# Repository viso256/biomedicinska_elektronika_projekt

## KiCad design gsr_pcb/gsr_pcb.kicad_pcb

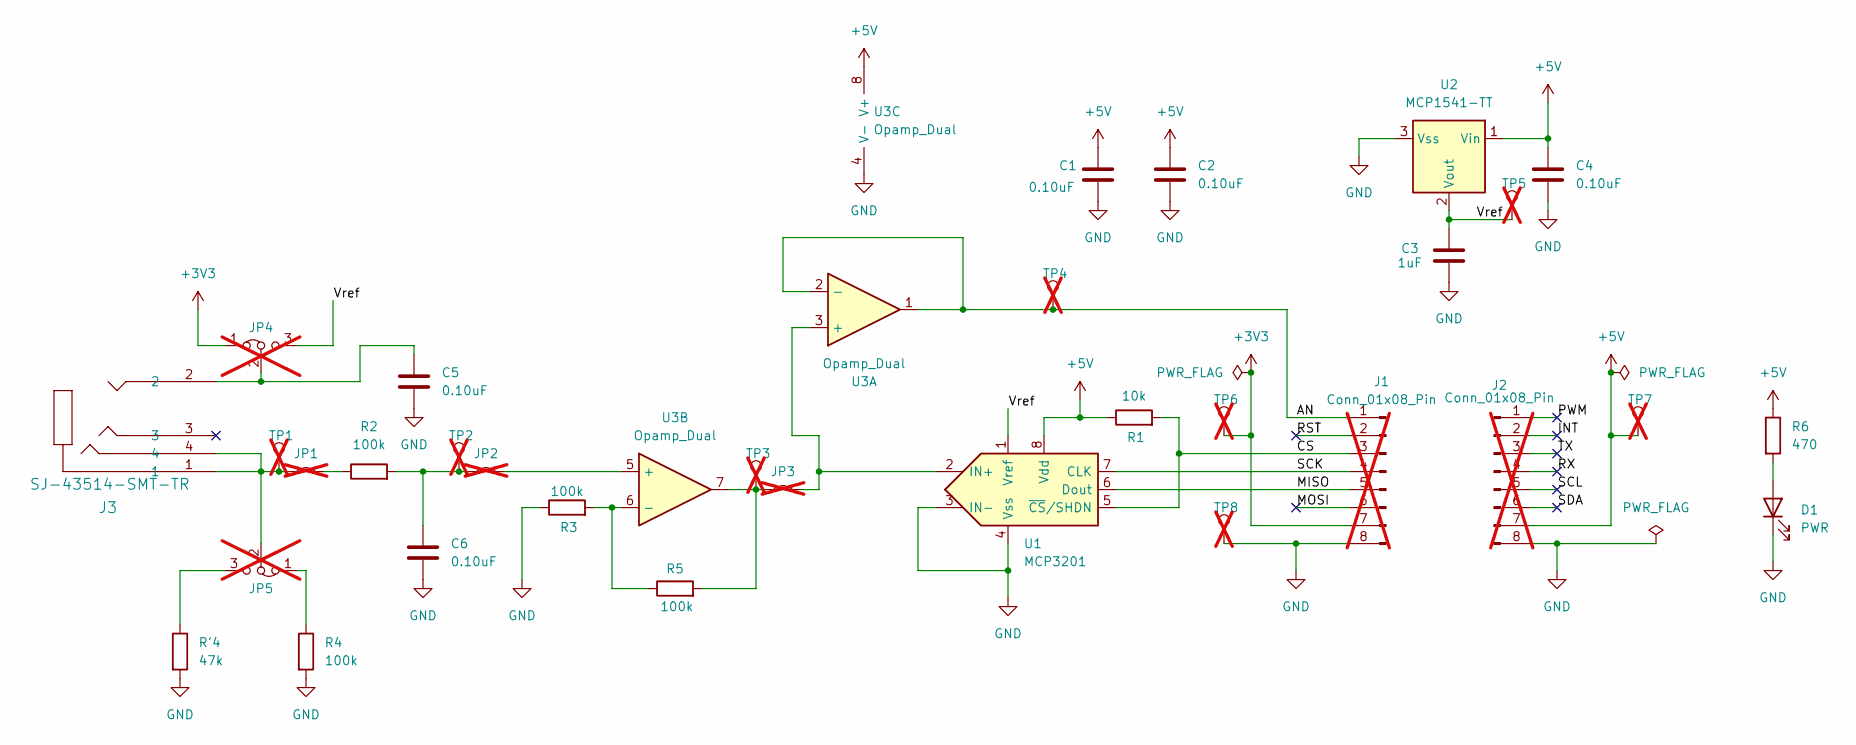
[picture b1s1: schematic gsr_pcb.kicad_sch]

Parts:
C1, C2, C4, C5, C6: 0.10uF; C_0603_1608Metric; LCSC C14663
C3: 1uF; C_0603_1608Metric; LCSC C15849
D1: PWR; LED_0805_2012Metric; LCSC C2297
J1, J2: Conn_01x08_Pin; PinHeader_1x08_P2.54mm_Vertical; not fitted
J3: SJ-43514-SMT-TR; SJ-43514-SMT_CUD; LCSC C4992301
JP1, JP2, JP3: Jumper_2_Small_Bridged; PinHeader_1x02_P2.54mm_Vertical; not fitted
JP4, JP5: Jumper_3_Bridged12; PinHeader_1x03_P2.54mm_Vertical; not fitted
R1: 10k; R_0603_1608Metric; LCSC C25804
R2, R3, R4, R5: 100k; R_0603_1608Metric; LCSC C25803
R6: 470; R_0603_1608Metric; LCSC C23179
R'4: 47k; R_0603_1608Metric; LCSC C25819
TP1, TP2, TP3, TP4, TP5, TP6, TP7, TP8: TestPoint; TestPoint_THTPad_D2.0mm_Drill1.0mm; not fitted
U1: MCP3201; SOIC8-N_MC_MCH; LCSC C49274
U2: MCP1541-TT; SOT-23; LCSC C7375
U3: Opamp_Dual; SOIC8-N_MC_MCH; LCSC C16279

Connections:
+3V3: J1.7, JP4.1 (A), TP6.1 (1_1)
+5V: C1.1, C2.1, C4.1, J2.7, R1.1, R6.1, TP7.1 (1_1), U1.8 (Vdd), U2.1 (Vin), U3.8 (V+)
/AN: J1.1, TP4.1 (1_1), U3.1, U3.2 (-)
/CS: J1.3, R1.2, U1.5 (~CS/SHDN)
/INT: J2.2
/MISO: J1.5, U1.6 (Dout)
/MOSI: J1.6
/PWM: J2.1
/RST: J1.2
/RX: J2.4
/SCK: J1.4, U1.7 (CLK)
/SCL: J2.5
/SDA: J2.6
/TX: J2.3
/Vref: C3.1, JP4.3 (B), TP5.1 (1_1), U1.1 (Vref), U2.2 (Vout)
GND: C1.2, C2.2, C3.2, C4.2, C5.2, C6.2, D1.1 (K), J1.8, J2.8, R3.1, R4.2, R'4.2, TP8.1 (1_1), U1.3 (IN-), U1.4 (Vss), U2.3 (Vss), U3.4 (V-)
unnamed: D1.2 (A), R6.2
unnamed: J3.1, J3.4, JP1.1 (A), JP5.2 (C), TP1.1 (1_1)
unnamed: JP1.2 (B), R2.1
unnamed: C6.1, JP2.1 (A), R2.2, TP2.1 (1_1)
unnamed: JP2.2 (B), U3.5 (+)
unnamed: JP3.1 (A), R5.2, TP3.1 (1_1), U3.7
unnamed: JP3.2 (B), U1.2 (IN+), U3.3 (+)
unnamed: C5.1, J3.2, JP4.2 (C)
unnamed: JP5.1 (A), R4.1
unnamed: JP5.3 (B), R'4.1
unnamed: R3.2, R5.1, U3.6 (-)

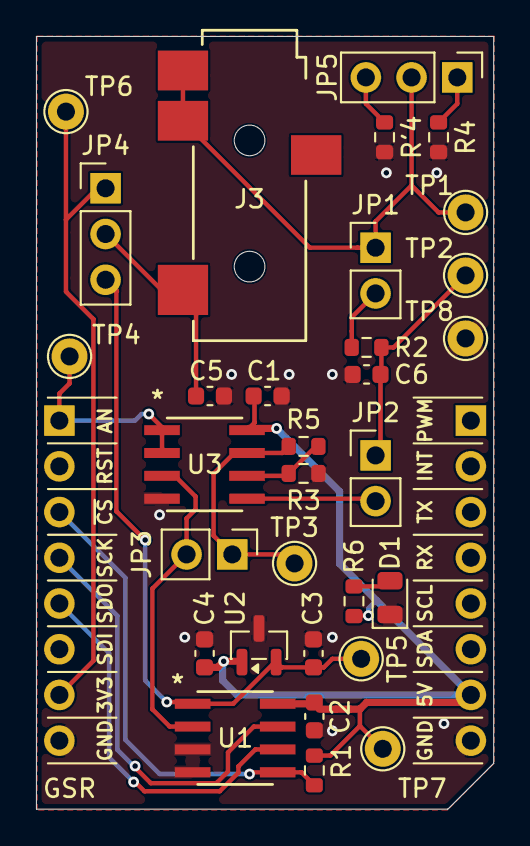
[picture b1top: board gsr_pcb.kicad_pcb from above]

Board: 2 copper layers, 25.4 x 42.9 mm, 33 parts (0 on the bottom side), 19 nets.

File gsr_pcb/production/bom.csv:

Designator,Footprint,Quantity,Value,LCSC Part #
"C1, C2, C4, C5, C6",0603,5,0.10uF,C14663
C3,0603,1,1uF,C15849
D1,0805,1,PWR,C2297
J3,SJ-43514-SMT_CUD,1,SJ-43514-SMT-TR,C4992301
R'4,0603,1,47k,C25819
R1,0603,1,10k,C25804
"R2, R3, R4, R5",0603,4,100k,C25803
R6,0603,1,470,C23179
U1,SOIC8-N_MC_MCH,1,MCP3201,C49274
U2,SOT-23,1,MCP1541-TT,C7375
U3,SOIC8-N_MC_MCH,1,Opamp_Dual,C16279
